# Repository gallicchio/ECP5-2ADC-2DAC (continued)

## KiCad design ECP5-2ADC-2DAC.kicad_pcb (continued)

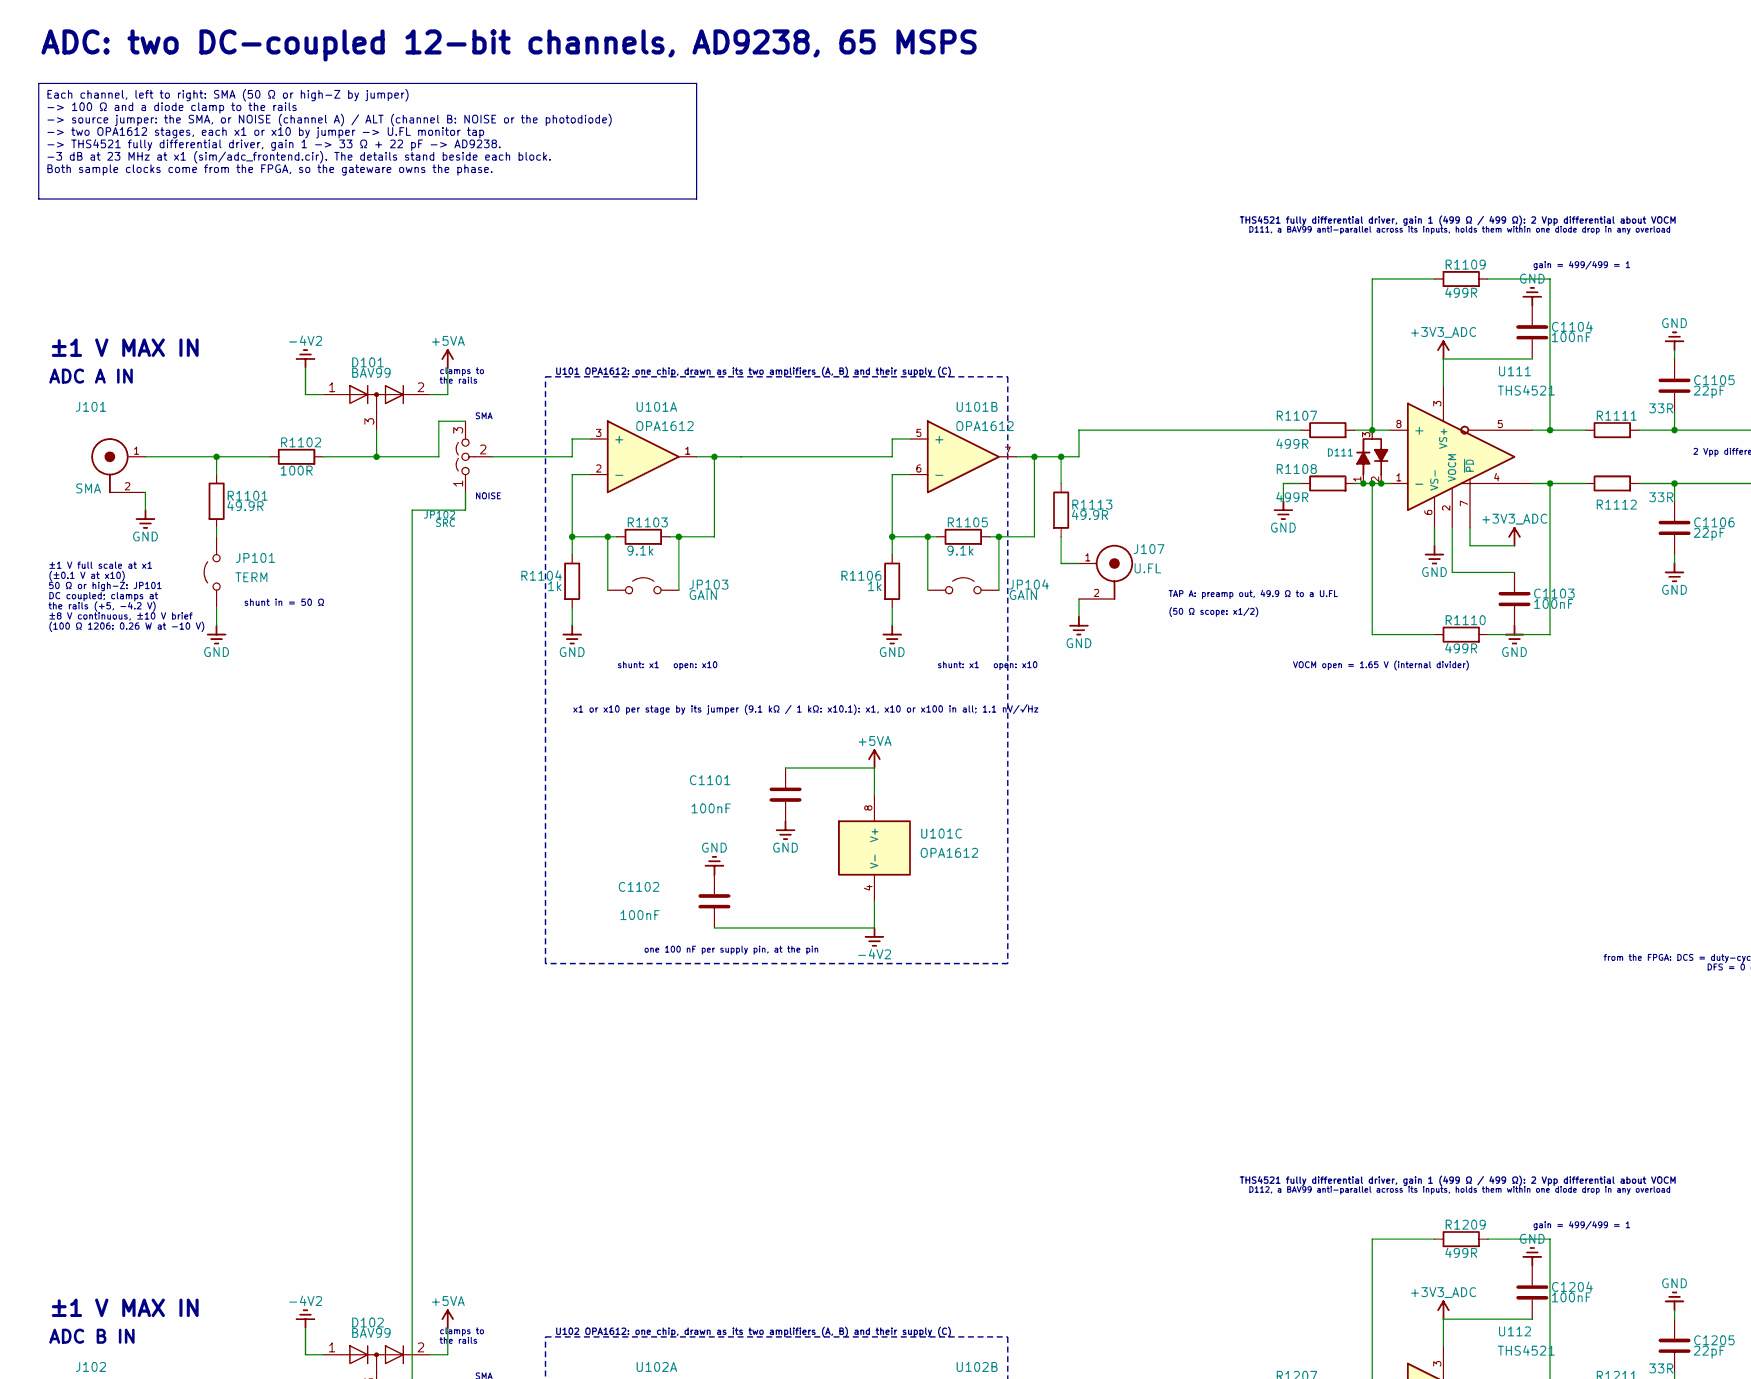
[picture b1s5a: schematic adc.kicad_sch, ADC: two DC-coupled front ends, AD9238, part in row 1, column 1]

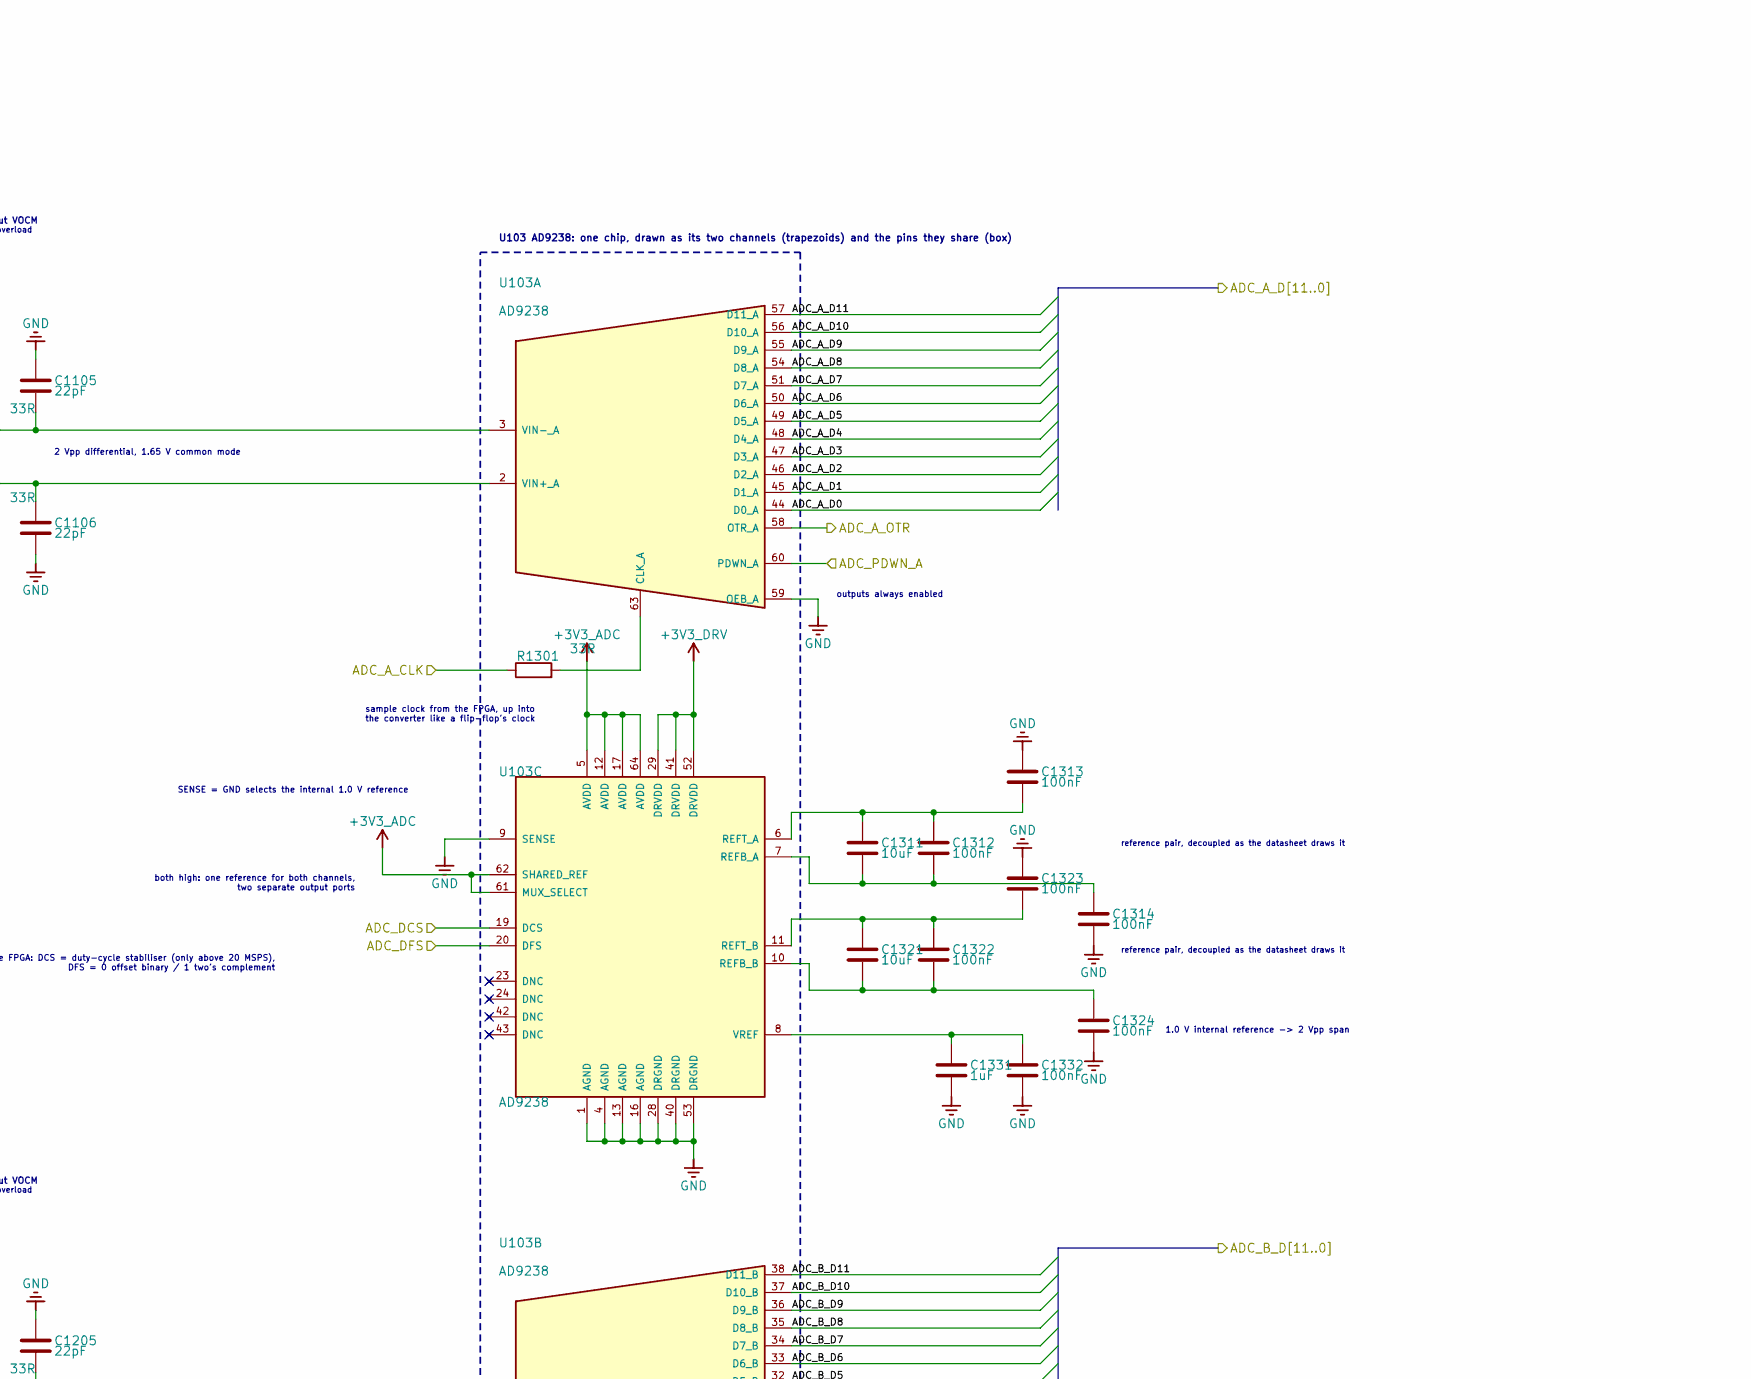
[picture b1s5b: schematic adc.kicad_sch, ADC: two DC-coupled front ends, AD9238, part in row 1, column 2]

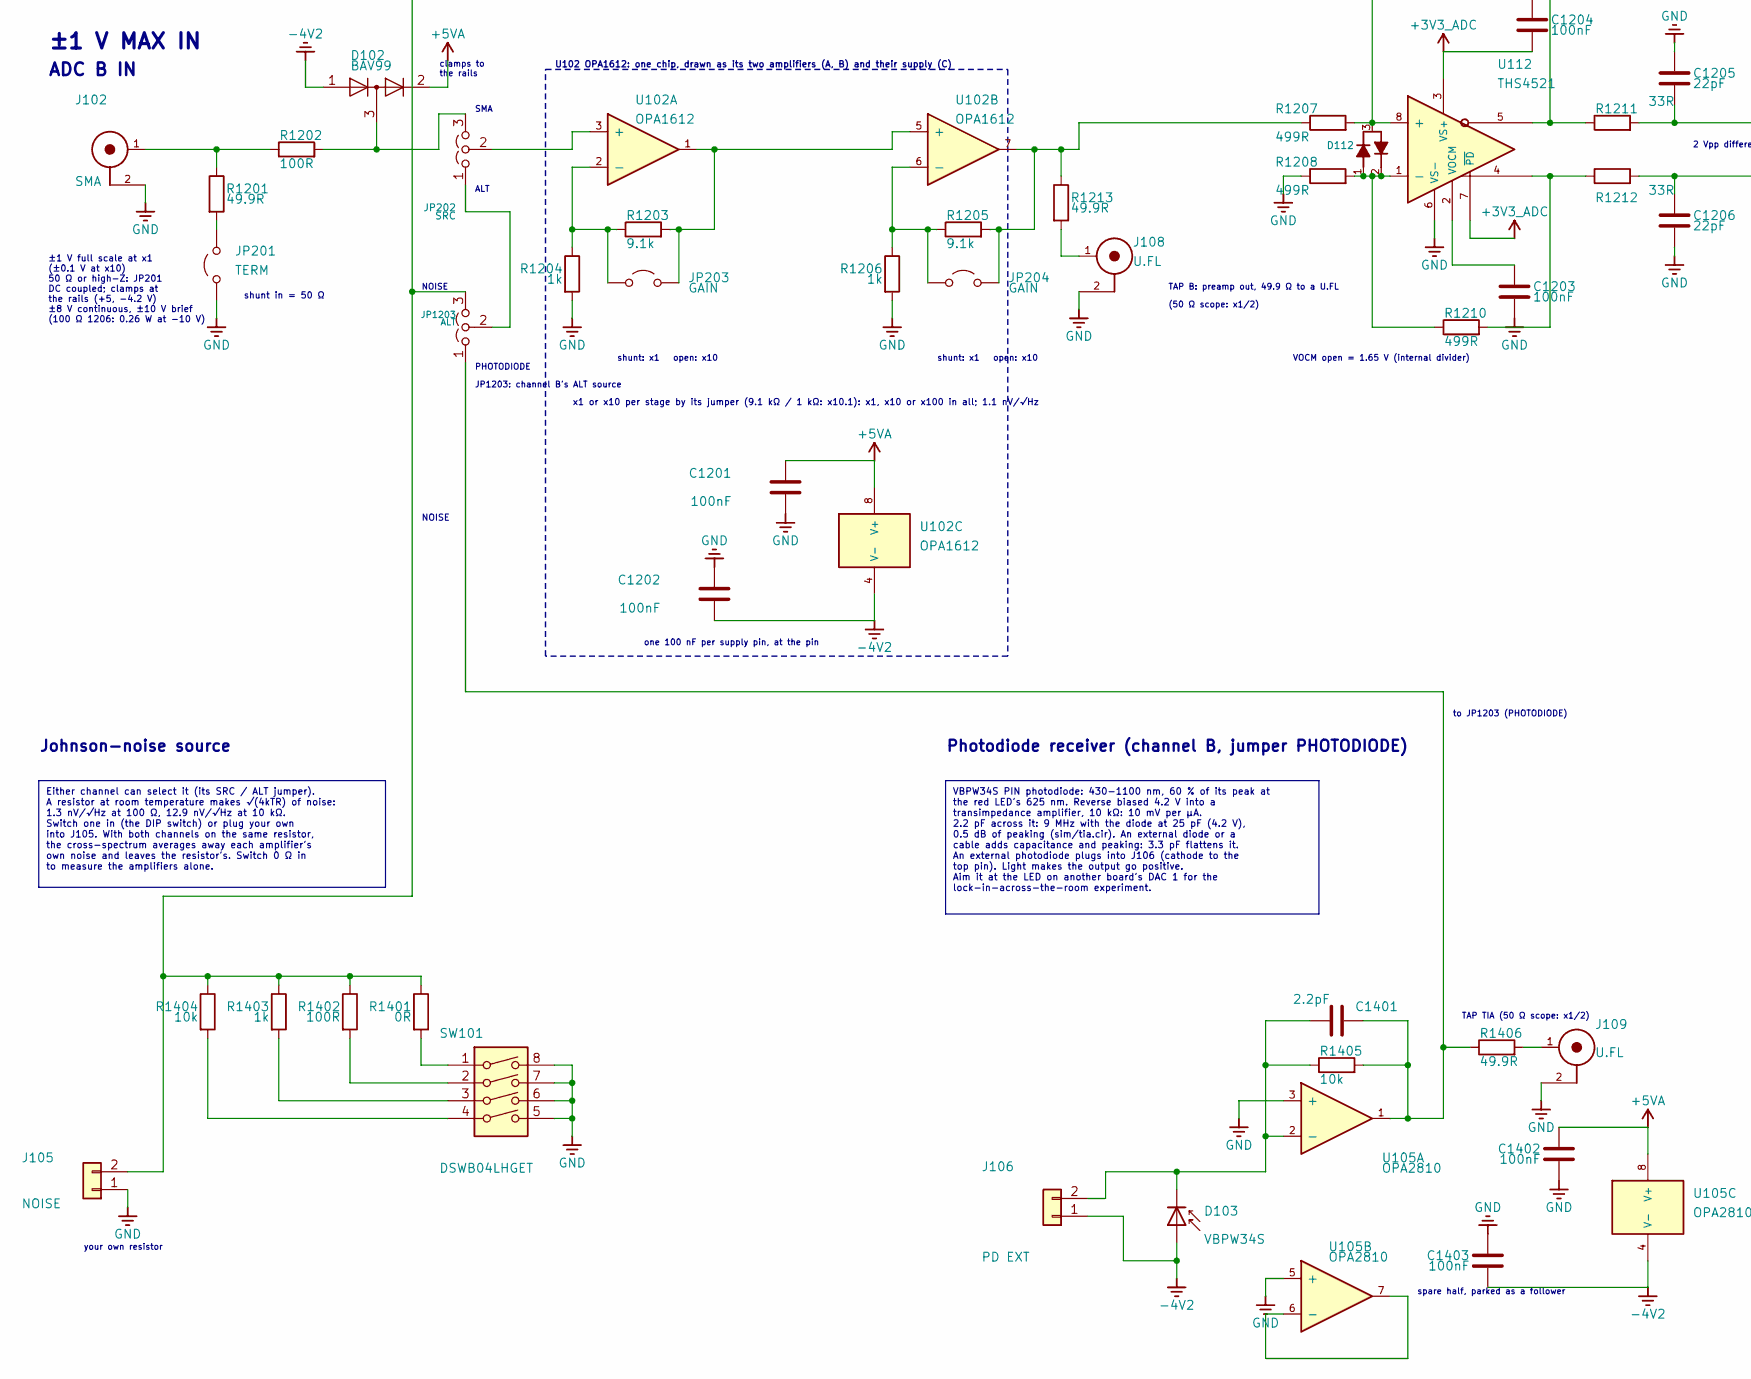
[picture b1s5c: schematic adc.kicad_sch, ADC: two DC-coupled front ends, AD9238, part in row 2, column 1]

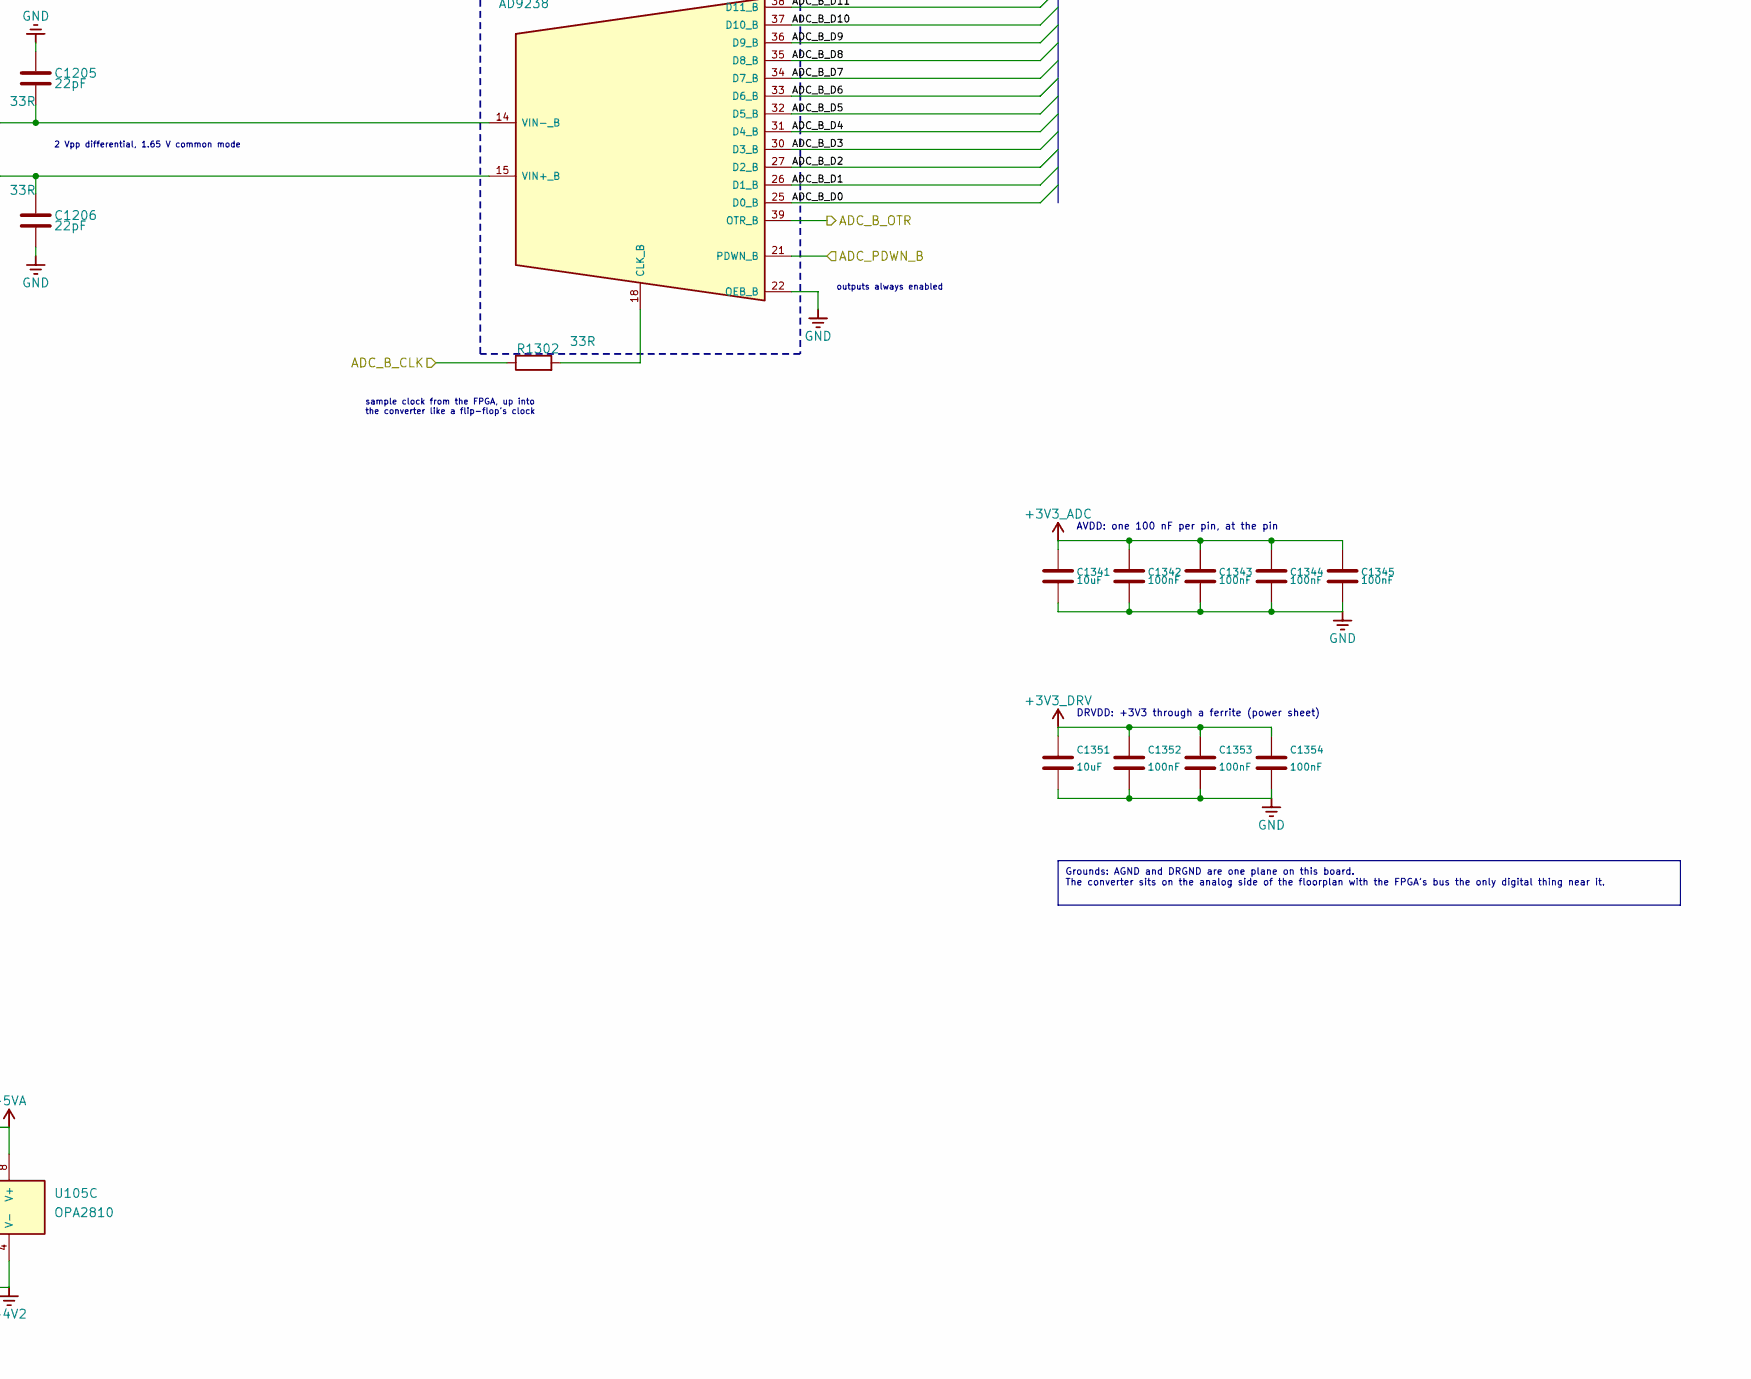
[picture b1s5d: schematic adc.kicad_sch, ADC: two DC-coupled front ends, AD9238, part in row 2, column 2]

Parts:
C1101, C1102, C1103, C1104, C1201, C1202, C1203, C1204, C1312, C1313, C1314, C1322, C1323, C1324, C1332, C1342, C1343, C1344, C1345, C1352, C1353, C1354, C1402, C1403: 100nF; C_0402_1005Metric; LCSC C1525
C1105, C1106, C1205, C1206: 22pF; C_0402_1005Metric; LCSC C1555
C1311, C1321, C1341, C1351: 10uF; C_0603_1608Metric; LCSC C96446
C1331: 1uF; C_0402_1005Metric; LCSC C52923
C1401: 2.2pF; C_0402_1005Metric; LCSC C1559
D101, D102, D111, D112: BAV99; SOT-23; LCSC C2500
D103: VBPW34S; VBPW34S_K1_A2; LCSC C145262
J101, J102: SMA; SMA_BAT_Wireless_BWSMA-KWE-Z001; LCSC C496551
J105: NOISE; PinHeader_1x02_P2.54mm_Vertical; LCSC C492401
J106: PD EXT; PinHeader_1x02_P2.54mm_Vertical; LCSC C492401
J107, J108, J109: U.FL; UFL_Hirose_U.FL-R-SMT-1; LCSC C88374
JP101, JP201: TERM; PinHeader_1x02_P2.54mm_Vertical; LCSC C492401
JP102, JP202: SRC; PinHeader_1x03_P2.54mm_Vertical; LCSC C2937625
JP103, JP104, JP203, JP204: GAIN; PinHeader_1x02_P2.54mm_Vertical; LCSC C492401
JP1203: ALT; PinHeader_1x03_P2.54mm_Vertical; LCSC C2937625
R1101, R1113, R1201, R1213, R1406: 49.9R; R_0603_1608Metric; LCSC C23185
R1102, R1202: 100R; R_1206_3216Metric; LCSC C17901
R1103, R1105, R1203, R1205: 9.1k; R_0603_1608Metric; LCSC C23260
R1104, R1106, R1204, R1206, R1403: 1k; R_0603_1608Metric; LCSC C21190
R1107, R1108, R1109, R1110, R1207, R1208, R1209, R1210: 499R; R_0603_1608Metric; LCSC C137714
R1111, R1112, R1211, R1212, R1301, R1302: 33R; R_0603_1608Metric; LCSC C23140
R1401: 0R; R_0603_1608Metric; LCSC C21189
R1402: 100R; R_0603_1608Metric; LCSC C22775
R1404, R1405: 10k; R_0603_1608Metric; LCSC C25804
SW101: DSWB04LHGET; SW-TH_DSWB04LHGET; LCSC C99418
U101, U102: OPA1612; SOIC-8_3.9x4.9mm_P1.27mm; LCSC C94590
U103: AD9238; LQFP-64_7x7mm_P0.4mm; LCSC C514277
U105: OPA2810; SOIC-8_3.9x4.9mm_P1.27mm; LCSC C1849413
U111, U112: THS4521; MSOP-8_3x3mm_P0.65mm; LCSC C170157

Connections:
+3V3_ADC: C1104.2, C1204.2, C1341.1, C1342.1, C1343.1, C1344.1, C1345.1, U103.5 (AVDD), U103.12 (AVDD), U103.17 (AVDD), U103.61 (MUX_SELECT), U103.62 (SHARED_REF), U103.64 (AVDD), U111.3 (VS+), U111.7 (~PD), U112.3 (VS+), U112.7 (~PD); also elsewhere on the board
+3V3_DRV: C1351.1, C1352.1, C1353.1, C1354.1, U103.29 (DRVDD), U103.41 (DRVDD), U103.52 (DRVDD); also elsewhere on the board
+5VA: C1101.1, C1201.1, C1402.1, D101.2 (A), D102.2 (A), U101.8 (V+), U102.8 (V+), U105.8 (V+); also elsewhere on the board
-4V2: C1102.2, C1202.2, C1403.2, D101.1 (K), D102.1 (K), D103.2 (A), J106.1, U101.4 (V-), U102.4 (V-), U105.4 (V-); also elsewhere on the board
/ADC/ADC_A_CLK: R1301.1; also elsewhere on the board
/ADC/ADC_A_D0: U103.44 (D0_A); also elsewhere on the board
/ADC/ADC_A_D1: U103.45 (D1_A); also elsewhere on the board
/ADC/ADC_A_D2: U103.46 (D2_A); also elsewhere on the board
/ADC/ADC_A_D3: U103.47 (D3_A); also elsewhere on the board
/ADC/ADC_A_D4: U103.48 (D4_A); also elsewhere on the board
/ADC/ADC_A_D5: U103.49 (D5_A); also elsewhere on the board
/ADC/ADC_A_D6: U103.50 (D6_A); also elsewhere on the board
/ADC/ADC_A_D7: U103.51 (D7_A); also elsewhere on the board
/ADC/ADC_A_D8: U103.54 (D8_A); also elsewhere on the board
/ADC/ADC_A_D9: U103.55 (D9_A); also elsewhere on the board
/ADC/ADC_A_D10: U103.56 (D10_A); also elsewhere on the board
/ADC/ADC_A_D11: U103.57 (D11_A); also elsewhere on the board
/ADC/ADC_A_OTR: U103.58 (OTR_A); also elsewhere on the board
/ADC/ADC_B_CLK: R1302.1; also elsewhere on the board
/ADC/ADC_B_D0: U103.25 (D0_B); also elsewhere on the board
/ADC/ADC_B_D1: U103.26 (D1_B); also elsewhere on the board
/ADC/ADC_B_D2: U103.27 (D2_B); also elsewhere on the board
/ADC/ADC_B_D3: U103.30 (D3_B); also elsewhere on the board
/ADC/ADC_B_D4: U103.31 (D4_B); also elsewhere on the board
/ADC/ADC_B_D5: U103.32 (D5_B); also elsewhere on the board
/ADC/ADC_B_D6: U103.33 (D6_B); also elsewhere on the board
/ADC/ADC_B_D7: U103.34 (D7_B); also elsewhere on the board
/ADC/ADC_B_D8: U103.35 (D8_B); also elsewhere on the board
/ADC/ADC_B_D9: U103.36 (D9_B); also elsewhere on the board
/ADC/ADC_B_D10: U103.37 (D10_B); also elsewhere on the board
/ADC/ADC_B_D11: U103.38 (D11_B); also elsewhere on the board
/ADC/ADC_B_OTR: U103.39 (OTR_B); also elsewhere on the board
/ADC/ADC_DCS: U103.19 (DCS); also elsewhere on the board
/ADC/ADC_DFS: U103.20 (DFS); also elsewhere on the board
/ADC/ADC_PDWN_A: U103.60 (PDWN_A); also elsewhere on the board
/ADC/ADC_PDWN_B: U103.21 (PDWN_B); also elsewhere on the board
GND: C1101.2, C1102.1, C1103.2, C1104.1, C1105.1, C1106.2, C1201.2, C1202.1, C1203.2, C1204.1, C1205.1, C1206.2, C1313.1, C1314.2, C1323.1, C1324.2, C1331.2, C1332.2, C1341.2, C1342.2, C1343.2, C1344.2, C1345.2, C1351.2, C1352.2, C1353.2, C1354.2, C1402.2, C1403.1, J101.2, J102.2, J105.1, J107.2, J108.2, J109.2, JP101.1 (A), JP201.1 (A), R1104.2, R1106.2, R1108.1, R1204.2, R1206.2, R1208.1, SW101.5, SW101.6, SW101.7, SW101.8, U103.1 (AGND), U103.4 (AGND), U103.9 (SENSE), U103.13 (AGND), U103.16 (AGND), U103.22 (OEB_B), U103.28 (DRGND), U103.40 (DRGND), U103.53 (DRGND), U103.59 (OEB_A), U105.3 (+), U105.5 (+), U111.6 (VS-), U112.6 (VS-); also elsewhere on the board
unnamed: C1401.1, D103.1 (K), J106.2, R1405.1, U105.2 (-)
unnamed: J101.1, R1101.1, R1102.1
unnamed: J102.1, R1201.1, R1202.1
unnamed: J105.2, JP102.1 (A), JP1203.3 (B), R1401.1, R1402.1, R1403.1, R1404.1
unnamed: J107.1, R1113.2
unnamed: J108.1, R1213.2
unnamed: J109.1, R1406.2
unnamed: JP101.2 (B), R1101.2
unnamed: D101.3 (K), JP102.3 (B), R1102.2
unnamed: JP102.2 (C), U101.3 (+)
unnamed: JP103.1 (A), R1103.1, R1104.1, U101.2 (-)
unnamed: JP103.2 (B), R1103.2, U101.1, U101.5 (+)
unnamed: JP104.1 (A), R1105.1, R1106.1, U101.6 (-)
unnamed: JP104.2 (B), R1105.2, R1107.1, R1113.1, U101.7
unnamed: JP201.2 (B), R1201.2
unnamed: D102.3 (K), JP202.3 (B), R1202.2
unnamed: JP202.2 (C), U102.3 (+)
unnamed: JP203.1 (A), R1203.1, R1204.1, U102.2 (-)
unnamed: JP203.2 (B), R1203.2, U102.1, U102.5 (+)
unnamed: JP204.1 (A), R1205.1, R1206.1, U102.6 (-)
unnamed: JP204.2 (B), R1205.2, R1207.1, R1213.1, U102.7
unnamed: C1401.2, JP1203.1 (A), R1405.2, R1406.1, U105.1
unnamed: JP202.1 (A), JP1203.2 (C)
unnamed: R1109.2, R1111.1, U111.5
unnamed: R1110.2, R1112.1, U111.4
unnamed: R1209.2, R1211.1, U112.5
unnamed: R1210.2, R1212.1, U112.4
unnamed: R1401.2, SW101.1
unnamed: R1402.2, SW101.2
unnamed: R1403.2, SW101.3
unnamed: R1404.2, SW101.4
unnamed: R1301.2, U103.63 (CLK_A)
unnamed: C1106.1, R1112.2, U103.2 (VIN+_A)
unnamed: C1105.2, R1111.2, U103.3 (VIN-_A)
unnamed: R1302.2, U103.18 (CLK_B)
unnamed: C1206.1, R1212.2, U103.15 (VIN+_B)
unnamed: C1205.2, R1211.2, U103.14 (VIN-_B)
unnamed: C1311.2, C1312.2, C1314.1, U103.7 (REFB_A)
unnamed: C1321.2, C1322.2, C1324.1, U103.10 (REFB_B)
unnamed: C1311.1, C1312.1, C1313.2, U103.6 (REFT_A)
unnamed: C1321.1, C1322.1, C1323.2, U103.11 (REFT_B)
unnamed: C1331.1, C1332.1, U103.8 (VREF)
unnamed: U105.6 (-), U105.7
unnamed: D111.3, R1107.2, R1109.1, U111.8 (+)
unnamed: D111.1, D111.2, R1108.2, R1110.1, U111.1 (-)
unnamed: C1103.1, U111.2 (VOCM)
unnamed: D112.3, R1207.2, R1209.1, U112.8 (+)
unnamed: D112.1, D112.2, R1208.2, R1210.1, U112.1 (-)
unnamed: C1203.1, U112.2 (VOCM)

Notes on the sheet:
1.0 V internal reference -> 2 Vpp span
shunt: x1 open: x10
AVDD: one 100 nF per pin, at the pin
±1 V full scale at x1 (±0.1 V at x10) 50 Ω or high-Z: JP101 DC coupled; clamps at the rails (+5, -4.2 V) ±8 V continuous, ±10 V brief (100 Ω 1206: 0.26 W at -10 V)
reference pair, decoupled as the datasheet draws it
sample clock from the FPGA, up into the converter like a flip-flop's clock
your own resistor
from the FPGA: DCS = duty-cycle stabiliser (only above 20 MSPS), DFS = 0 offset binary / 1 two's complement
to JP1203 (PHOTODIODE)
U103 AD9238: one chip, drawn as its two channels (trapezoids) and the pins they share (box)
±1 V full scale at x1 (±0.1 V at x10) 50 Ω or high-Z: JP201 DC coupled; clamps at the rails (+5, -4.2 V) ±8 V continuous, ±10 V brief (100 Ω 1206: 0.26 W at -10 V)
ADC: two DC-coupled 12-bit channels, AD9238, 65 MSPS
D112, a BAV99 anti-parallel across its inputs, holds them within one diode drop in any overload
THS4521 fully differential driver, gain 1 (499 Ω / 499 Ω): 2 Vpp differential about VOCM
NOISE
Johnson-noise source
clamps to the rails
(50 Ω scope: x1/2)
PHOTODIODE
outputs always enabled
SMA
spare half, parked as a follower
U102 OPA1612: one chip, drawn as its two amplifiers (A, B) and their supply (C)
SENSE = GND selects the internal 1.0 V reference
both high: one reference for both channels, two separate output ports
VOCM open = 1.65 V (internal divider)
D111, a BAV99 anti-parallel across its inputs, holds them within one diode drop in any overload
shunt in = 50 Ω
±1 V MAX IN
2 Vpp differential, 1.65 V common mode
gain = 499/499 = 1
DRVDD: +3V3 through a ferrite (power sheet)
ALT
TAP B: preamp out, 49.9 Ω to a U.FL
ADC B IN
JP1203: channel B's ALT source
x1 or x10 per stage by its jumper (9.1 kΩ / 1 kΩ: x10.1): x1, x10 or x100 in all; 1.1 nV/√Hz
ADC A IN
one 100 nF per supply pin, at the pin
Photodiode receiver (channel B, jumper PHOTODIODE)
